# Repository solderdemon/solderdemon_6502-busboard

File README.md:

# SolderDemon 6502 Bus Board

## Overview

A 5-slot expansion busboard for the SolderDemon 6502 computer. The 36-pin bus keeps the [rosco_6502](https://github.com/rosco-m68k/rosco_6502) pin order, so cards made for that bus fit.

Designed as a modular vertical-card backplane architecture featuring 1 dedicated host connection for the SolderDemon 6502 CPU board and 4 peripheral expansion slots (e.g., RAM boards, I/O controllers), along with flexible 5V power delivery and host isolation options.

## Start here

- [KiCad project](design/solderdemon_6502-busboard.kicad_pro)
- [Schematic (PDF)](manufacturing/solderdemon_6502-busboard-schematic.pdf)
- [Host mounting and first build](#host-mounting-and-first-build)
- [Gerbers and drill files](manufacturing/solderdemon_6502-busboard-gerbers.zip)
- [Assembly BOM](manufacturing/bom.csv)

## Board views

*Prototype photo with edited background and lighting.*

| Top Side | Bottom Side |
|:---:|:---:|
|  |  |

## Hardware

### Highlights

- **Slot Architecture:** 1 Host Slot (`BUS1`) + 4 Expansion Slots (`BUS2`–`BUS5` = SLOT 1–4, each with its 100 nF `C3`–`C6`) using standard 2×18 vertical pin headers (2.54 mm / 0.1" pitch, 20 mm slot pitch). The host and the cards stand upright in their slots on right-angle 2×18 sockets, all facing the same way; a silkscreen triangle marks pin 1 of every slot; as on the SolderDemon m68k busboard, each slot's decoupler stands on the half-pitch line to its right, beside pin 1, clear of every board plane
- **Power Inputs:** Triple 5V power input options:
  - USB Type-C receptacle (`J3`, USB 2.0 power delivery with onboard 5.1 kΩ CC pull-downs)
  - 5.5 / 2.1 mm DC Barrel Jack (`J1`, center-positive)
  - 2-pin screw terminal / vertical header block (`J2`, 5V IN)
- **Source Selection:** one jumper cap on the 2×3 header `JP2` picks the input: the USB, DC or TERM row, in the order of the inputs down the right edge (USB-C, DC jack, then the terminal `J2` under the jack). No diodes, so no 0.3–0.6 V drop: the bus gets the supply voltage. Never fit two source jumpers
- **Protection:** a 1.5KE6.8A unidirectional TVS (`D1`) from `VCC` to GND. There is no fuse: a reversed or wrong-voltage adapter is shorted by `D1`, and only the adapter's own current limit stops it
- **Power Control & Filtering:** NKK M2021SS1W01 DPST toggle (`SW1`, the switch of the SolderDemon m68k busboard; both poles in parallel), PWR GOOD LED indicator (`LED1`), 470 µF bulk electrolytic reservoir (`C1`), five 100 nF bypass capacitors (`C2`–`C6`) and the bus `~RESET` pull-up `R2` with `C7`
- **Host Power Isolation (`JP1`):** Allows powering the host SBC independently (e.g., via USB serial adapter) while powering peripheral slots from the backplane
- **Form Factor:** 137 × 100 mm 2-layer PCB, all through-hole components (except USB-C receptacle) for straightforward DIY assembly
- **Mounting:** 6× M3 mounting holes with grounded annular pads, three along each long edge: the four corners plus the middle of the top and bottom edge, halfway between the corner holes

### Pinout

The busboard exposes the 36-pin SolderDemon 6502 bus (rosco_6502-compatible pin order) across all five slots:

| Pin | Signal | Description | Pin | Signal | Description |
|:---:|:---|:---|:---:|:---|:---|
| **1** | **A0** | Address Bus bit 0 (square pad) | **2** | **VCC / VCC_HOST** | +5V Power Rail (Host isolated via JP1) |
| **3** | **A1** | Address Bus bit 1 | **4** | **CLK** | CPU Phase 2 System Clock (PHI2) |
| **5** | **A2** | Address Bus bit 2 | **6** | **GND** | System Ground (0V) |
| **7** | **A3** | Address Bus bit 3 | **8** | **R/~W** | Read / ~Write Control Line |
| **9** | **A4** | Address Bus bit 4 | **10** | **~RESET** | Active-Low System Reset |
| **11** | **A5** | Address Bus bit 5 | **12** | **RDY** | 65C02 CPU Ready Line |
| **13** | **A6** | Address Bus bit 6 | **14** | **~NMI** | Non-Maskable Interrupt Request |
| **15** | **A7** | Address Bus bit 7 | **16** | **~IRQ** | Maskable Interrupt Request |
| **17** | **A8** | Address Bus bit 8 | **18** | **SYNC** | Opcode Fetch Cycle Indicator |
| **19** | **A9** | Address Bus bit 9 | **20** | **BE** | Bus Enable Line |
| **21** | **A10** | Address Bus bit 10 | **22** | **D7** | Data Bus bit 7 |
| **23** | **A11** | Address Bus bit 11 | **24** | **D6** | Data Bus bit 6 |
| **25** | **A12** | Address Bus bit 12 | **26** | **D5** | Data Bus bit 5 |
| **27** | **A13** | Address Bus bit 13 | **28** | **D4** | Data Bus bit 4 |
| **29** | **A14** | Address Bus bit 14 | **30** | **D3** | Data Bus bit 3 |
| **31** | **A15** | Address Bus bit 15 | **32** | **D2** | Data Bus bit 2 |
| **33** | **~VP** | Vector Pull Indicator | **34** | **D1** | Data Bus bit 1 |
| **35** | **~ML** | Memory Lock Indicator | **36** | **D0** | Data Bus bit 0 |

#### Power Interfaces & Control

| Designator | Label | Type / Footprint | Description |
|:---|:---|:---|:---|
| **J1** | DC IN | Barrel Jack 5.5 / 2.1 mm | 5V DC power input (center-positive) |
| **J2** | 5V IN | Pin Header / Terminal 1×02 | Auxiliary 5V DC power input, on the right edge under the DC jack |
| **J3** | USB-C 5V | USB Type-C Receptacle | 5V DC USB power input with CC pull-down resistors |
| **JP2** | SOURCE | Pin Header 2×03, 2.54 mm | Source select: one jumper cap across the USB, DC or TERM row |
| **SW1** | POWER | NKK M2021SS1W01 DPST toggle | Main power ON / OFF switch |
| **JP1** | PWR LINK | Pin Header 1×02, 2.54 mm | Power link jumper: links `VCC_HOST` to bus `VCC` |

> **Note on JP1 (PWR LINK):** When jumpered (default), all slots share the busboard 5V rail. When unjumpered, the host slot (`BUS1`) receives power from its own onboard source or serial adapter, preventing current loops while still sharing ground and signals.

## Using the board

### Host mounting and first build

The SolderDemon 6502 r1 host carries a right-angle female 2×18 socket on its J5 pads (KiCad `PinSocket_2x18_P2.54mm_Horizontal`; pin 2 is the pad nearer the body, i.e. the pads are the stock header mirrored) and stands upright in HOST, component side toward the busboard's left edge, its top edge level with the busboard's top edge. The compact SolderDemon 6502 RAM card uses the mirrored socket on B.Cu at its **right** edge and stands with its component side toward the next slot. Its pin 1 must align with the triangle at the top of the slot; all 36 contacts and the mirrored footprint geometry are checked against the current PCB files by its `tools/check_design.py`. Bolt the busboard through its six M3 holes to a case or rigid base before inserting any board. Do not connect J5 to HOST with a ribbon cable instead: because J5's pin order is mirrored for the socket, a plain 36-way ribbon between J5 and the straight HOST header swaps every odd/even pair and puts `VCC` on `A0`. The mating model (contact-row heights, edge height, clearances) is in [BACKPLANE.md](BACKPLANE.md).

The selected input carries the full board load through `SW1`; measure total current and voltage at the farthest slot before populating all five slots. The first order should be a prototype run, followed by pin-1 continuity, power and loaded-voltage checks.

## Build and verification

### Bill of Materials (BOM)

| Reference | Value | Package / Footprint | Notes |
|:---|:---|:---|:---|
| **BUS1–BUS5** | Conn_02x18 | PinHeader 2×18, 2.54 mm, Vertical | Host slot (`BUS1`) & 4 expansion slots (`BUS2`–`BUS5`) |
| **J1** | Barrel Jack | BarrelJack_Horizontal 5.5 / 2.1 mm | 5V DC input |
| **J2** | Conn_01x02 | PinHeader 1×02, 2.54 mm, Vertical | Auxiliary 5V screw terminal or pin header |
| **J3** | USB-C 16P | USB4105-xx-A Top Mount | USB Type-C 5V power receptacle |
| **JP1** | Conn_01x02 | PinHeader 1×02, 2.54 mm, Vertical | PWR LINK host power isolation jumper |
| **JP2** | Conn_02x03 + one jumper cap | PinHeader 2×03, 2.54 mm, Vertical | Source select: odd pins 1 terminal, 3 DC jack, 5 USB-C; even pins the common input |
| **D1** | 1.5KE6.8A | DO-201AE, Axial (THT) | Unidirectional TVS, 5.8 V standoff, across `VCC` |
| **SW1** | NKK M2021SS1W01 | NKK-M2021SS1W01 (SolderDemon.pretty) | DPST ON-OFF toggle, both poles in parallel; as on the m68k busboard |
| **LED1** | LED 5 mm | Radial D5.0 mm (THT) | PWR GOOD 5V rail status indicator |
| **C1** | 470 µF | Radial D6.3 mm, P2.5 mm | Bulk electrolytic reservoir capacitor |
| **C2–C6** | 100 nF | Radial 5.08 mm pitch | Decoupling: `C2` HOST, `C3`–`C6` SLOT 1–4 |
| **C7** | 1 nF | Disc D5.0 mm, P2.5 mm | Bus `~RESET` noise capacitor, with `R2`. Small on purpose: the host drives `~RESET` open-drain from its CPLD with its own 3.3 kΩ pull-up, and 100 nF would dump into that pin on every reset and stretch the release to ~250 µs |
| **R1** | 1 kΩ | Axial DIN0207, P10.16 mm | Current-limiting resistor for LED1 |
| **R2** | 10 kΩ | Axial DIN0207, P10.16 mm | Bus `~RESET` pull-up |
| **R3, R4** | 5.1 kΩ | Axial DIN0207, P10.16 mm | USB Type-C CC1 / CC2 pull-down resistors |
| **H1–H6** | Mounting Hole | 3.2 mm M3 with Ground Pad | Corners (`H1`–`H4`), middle of the top and bottom edge (`H5`, `H6`) |

### Manufacturing & Hardware Files

- **KiCad Project:** [design/](design/)
- **Footprint Libraries:** `SolderDemon.pretty/` (logo), `SolderDemonBus.pretty/`, `SolderDemonDirectMount.pretty/`
- **Schematic PDF:** [SolderDemon 6502 busboard schematic](manufacturing/solderdemon_6502-busboard-schematic.pdf)
- **Gerbers:**
  - Prototype fabrication archive: [solderdemon_6502-busboard-gerbers.zip](manufacturing/solderdemon_6502-busboard-gerbers.zip)
  - Unpacked fresh layers in [manufacturing/gerber/](manufacturing/gerber/) folder
- **PCB Specs:** 2-layer board, 137 × 100 mm, 1.6 mm thickness, standard 1 oz copper, HASL / ENIG finish
- **Design Verification:** [DRC Report](solderdemon_6502-busboard-drc.rpt) (KiCad 10.0.8 reports 4 hole-clearance errors at J3, 0 unrouted pads and 35 schematic-parity warnings), [ERC Report](solderdemon_6502-busboard-erc.rpt) (0 violations)
- **Backplane Specification:** [BACKPLANE.md](BACKPLANE.md) — mechanical dimensions, slot spacing, connector mating, and daughterboard form factor guidelines.

### Fabrication status

The current files are for prototype review. KiCad 10.0.8 reports four hole-clearance errors at USB-C connector J3. Review those clearances before fabrication.

<!-- repository-layout -->
## Repository layout

- [`design/`](design/solderdemon_6502-busboard.kicad_pro) holds the KiCad project, schematic, PCB and local libraries.
- [`code/firmware/`](code/firmware/) — This busboard has no programmable devices.
- [`code/software/`](code/software/) — The backplane requires no drivers or applications.
- [`code/build/`](code/build/) — Local build products.
- [`tools/`](tools/) — Design generators and verification.
- [`manufacturing/`](manufacturing/) — Fabrication files and schematic PDF.
- [`images/`](images/) — Board views and artwork.

Open the project in `design/`. Use the scripts in `tools/` to change the design. The `.kicad_pro` file holds the DRC rules.
<!-- /repository-layout -->

## Licences and attribution

- **Hardware:** [CERN Open Hardware Licence v1.2](LICENCE.hardware.txt).
- **Documentation:** [Creative Commons Attribution 4.0](https://creativecommons.org/licenses/by/4.0/).

SolderDemon backplane for the [rosco_6502](https://github.com/rosco-m68k/rosco_6502) expansion interface. Original rosco_6502 authorship: Ross Bamford & Contributors. Retained source and third-party notices identify their respective authors.

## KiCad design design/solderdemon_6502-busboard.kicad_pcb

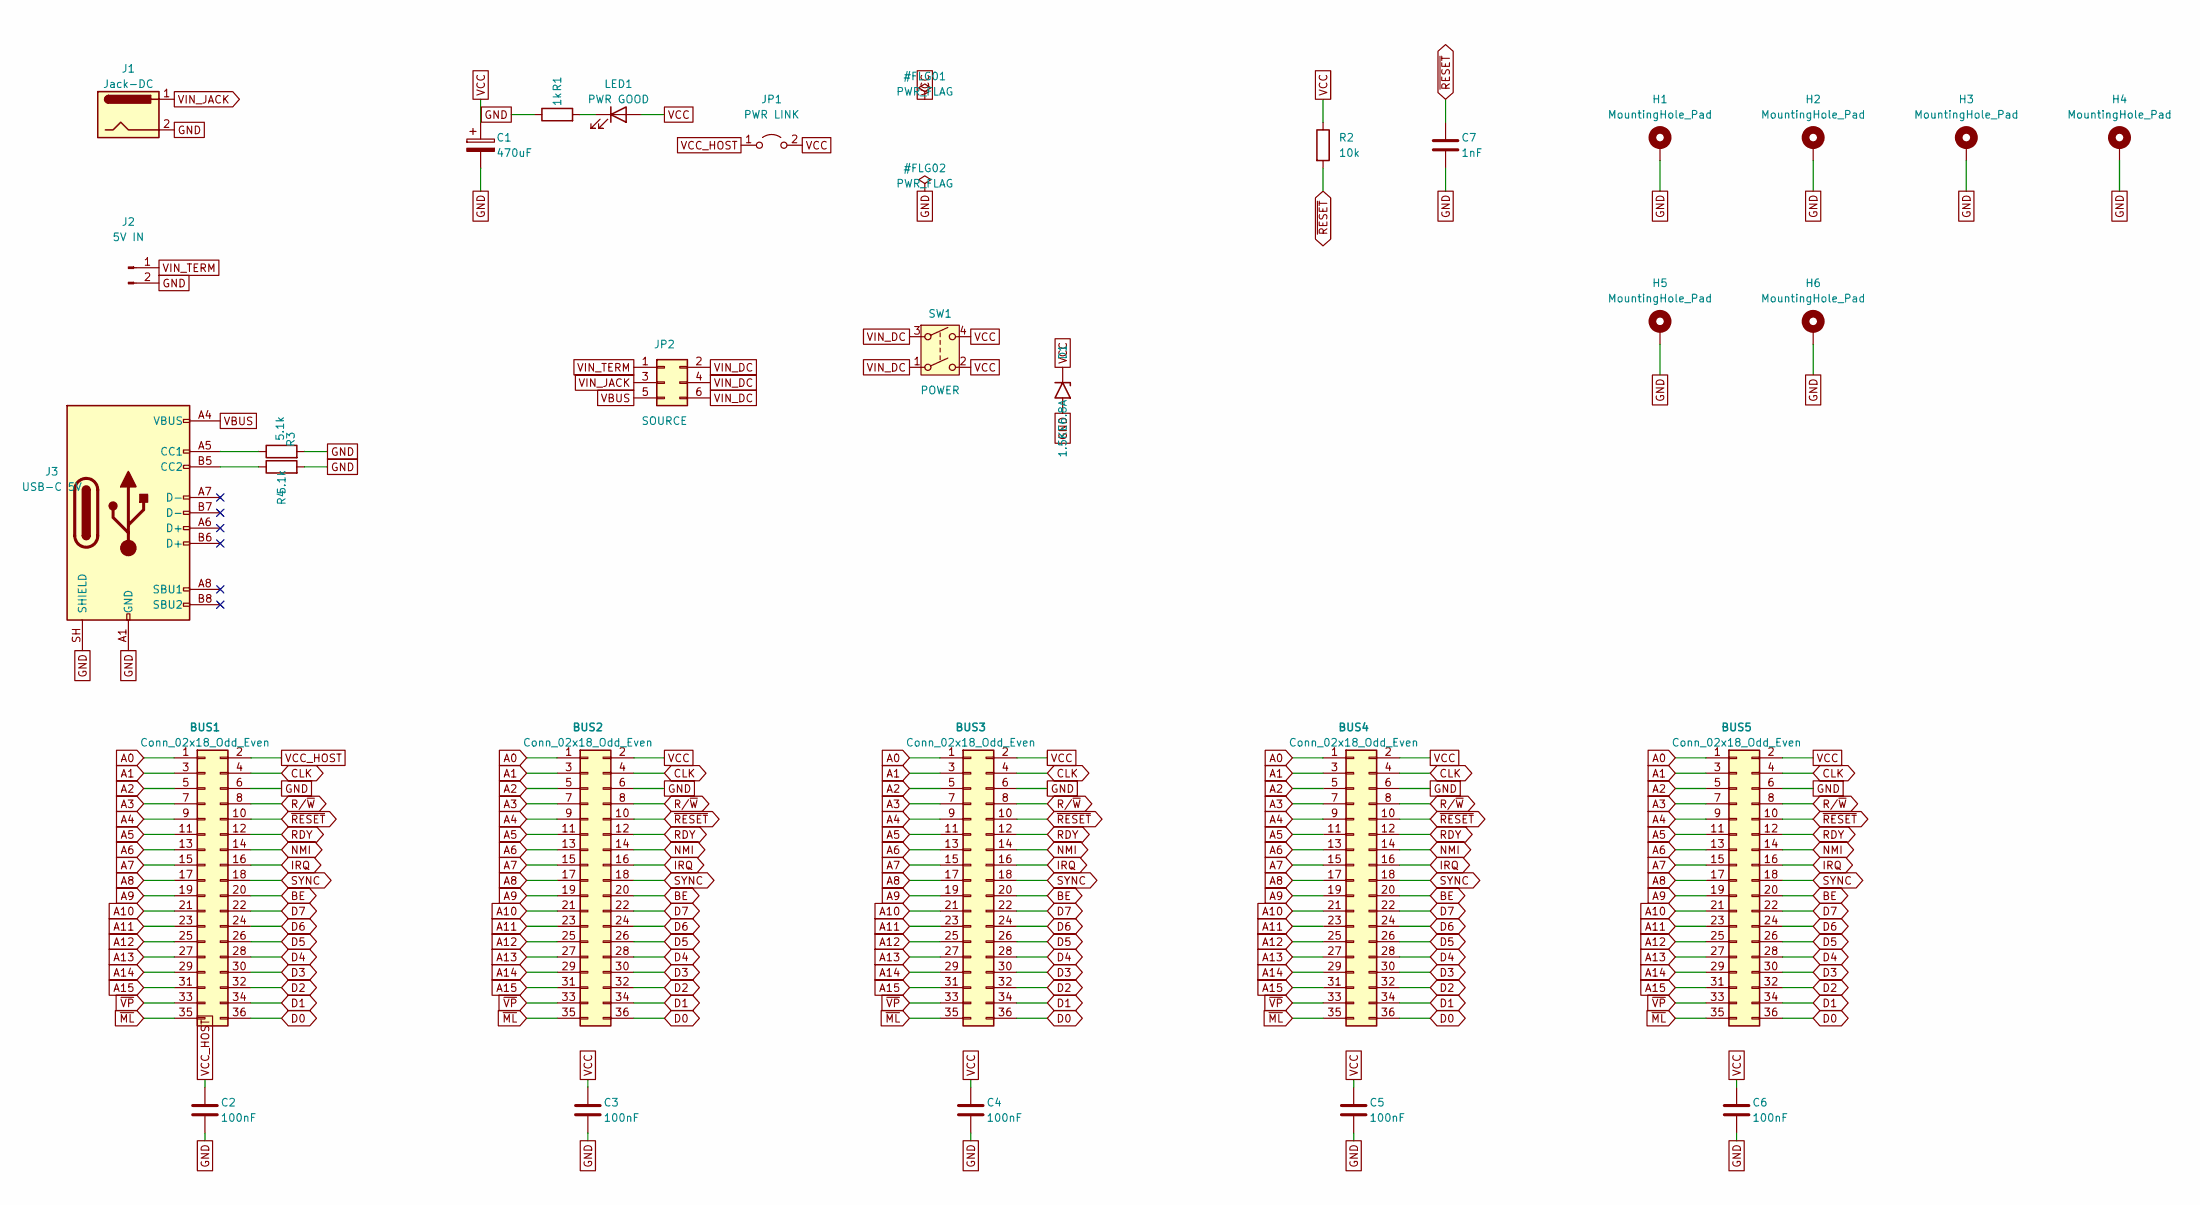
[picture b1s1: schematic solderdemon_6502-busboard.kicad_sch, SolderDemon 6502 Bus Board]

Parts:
BUS1, BUS2, BUS3, BUS4, BUS5: Conn_02x18_Odd_Even; PinHeader_2x18_P2.54mm_Vertical
C1: 470uF; CP_Radial_D6.3mm_P2.50mm
C2, C3, C4, C5, C6: 100nF; C_Radial_5.08mm
C7: 1nF; C_Disc_D5.0mm_W2.5mm_P2.50mm
D1: 1.5KE6.8A; D_DO-201AE_P15.24mm_Horizontal
H1, H2, H3, H4, H5, H6: MountingHole_Pad; MountingHole_3.2mm_M3_Pad
J1: Jack-DC; BarrelJack_Horizontal
J2: 5V IN; PinHeader_1x02_P2.54mm_Vertical
J3: USB-C 5V; USB_C_Receptacle_GCT_USB4105-xx-A_16P_TopMnt_Horizontal
JP1: PWR LINK; PinHeader_1x02_P2.54mm_Vertical
JP2: SOURCE; PinHeader_2x03_P2.54mm_Vertical
LED1: PWR GOOD; LED_D5.0mm
R1: 1k; R_Axial_DIN0207_L6.3mm_D2.5mm_P10.16mm_Horizontal
R2: 10k; R_Axial_DIN0207_L6.3mm_D2.5mm_P10.16mm_Horizontal
R3, R4: 5.1k; R_Axial_DIN0207_L6.3mm_D2.5mm_P10.16mm_Horizontal
SW1: POWER; NKK-M2021SS1W01

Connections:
A0: BUS1.1, BUS2.1, BUS3.1, BUS4.1, BUS5.1
A1: BUS1.3, BUS2.3, BUS3.3, BUS4.3, BUS5.3
A2: BUS1.5, BUS2.5, BUS3.5, BUS4.5, BUS5.5
A3: BUS1.7, BUS2.7, BUS3.7, BUS4.7, BUS5.7
A4: BUS1.9, BUS2.9, BUS3.9, BUS4.9, BUS5.9
A5: BUS1.11, BUS2.11, BUS3.11, BUS4.11, BUS5.11
A6: BUS1.13, BUS2.13, BUS3.13, BUS4.13, BUS5.13
A7: BUS1.15, BUS2.15, BUS3.15, BUS4.15, BUS5.15
A8: BUS1.17, BUS2.17, BUS3.17, BUS4.17, BUS5.17
A9: BUS1.19, BUS2.19, BUS3.19, BUS4.19, BUS5.19
A10: BUS1.21, BUS2.21, BUS3.21, BUS4.21, BUS5.21
A11: BUS1.23, BUS2.23, BUS3.23, BUS4.23, BUS5.23
A12: BUS1.25, BUS2.25, BUS3.25, BUS4.25, BUS5.25
A13: BUS1.27, BUS2.27, BUS3.27, BUS4.27, BUS5.27
A14: BUS1.29, BUS2.29, BUS3.29, BUS4.29, BUS5.29
A15: BUS1.31, BUS2.31, BUS3.31, BUS4.31, BUS5.31
BE: BUS1.20, BUS2.20, BUS3.20, BUS4.20, BUS5.20
CLK: BUS1.4, BUS2.4, BUS3.4, BUS4.4, BUS5.4
D0: BUS1.36, BUS2.36, BUS3.36, BUS4.36, BUS5.36
D1: BUS1.34, BUS2.34, BUS3.34, BUS4.34, BUS5.34
D2: BUS1.32, BUS2.32, BUS3.32, BUS4.32, BUS5.32
D3: BUS1.30, BUS2.30, BUS3.30, BUS4.30, BUS5.30
D4: BUS1.28, BUS2.28, BUS3.28, BUS4.28, BUS5.28
D5: BUS1.26, BUS2.26, BUS3.26, BUS4.26, BUS5.26
D6: BUS1.24, BUS2.24, BUS3.24, BUS4.24, BUS5.24
D7: BUS1.22, BUS2.22, BUS3.22, BUS4.22, BUS5.22
GND: BUS1.6, BUS2.6, BUS3.6, BUS4.6, BUS5.6, C1.2, C2.2, C3.2, C4.2, C5.2, C6.2, C7.2, D1.2 (A2), H1.1, H2.1, H3.1, H4.1, H5.1, H6.1, J1.2, J2.2, J3.A1 (GND), J3.A12 (GND), J3.B1 (GND), J3.B12 (GND), J3.SH (SHIELD), R1.1, R3.2, R4.2
IRQ: BUS1.16, BUS2.16, BUS3.16, BUS4.16, BUS5.16
NMI: BUS1.14, BUS2.14, BUS3.14, BUS4.14, BUS5.14
unnamed: J3.A5 (CC1), R3.1
unnamed: J3.B5 (CC2), R4.1
unnamed: LED1.1 (K), R1.2
RDY: BUS1.12, BUS2.12, BUS3.12, BUS4.12, BUS5.12
R/~W: BUS1.8, BUS2.8, BUS3.8, BUS4.8, BUS5.8
SYNC: BUS1.18, BUS2.18, BUS3.18, BUS4.18, BUS5.18
VBUS: J3.A4 (VBUS), J3.A9 (VBUS), J3.B4 (VBUS), J3.B9 (VBUS), JP2.5
VCC: BUS2.2, BUS3.2, BUS4.2, BUS5.2, C1.1, C3.1, C4.1, C5.1, C6.1, D1.1 (A1), JP1.2 (B), LED1.2 (A), R2.1, SW1.2, SW1.4
VCC_HOST: BUS1.2, C2.1, JP1.1 (A)
VIN_DC: JP2.2, JP2.4, JP2.6, SW1.1, SW1.3
VIN_JACK: J1.1, JP2.3
VIN_TERM: J2.1, JP2.1
~ML: BUS1.35, BUS2.35, BUS3.35, BUS4.35, BUS5.35
~RESET: BUS1.10, BUS2.10, BUS3.10, BUS4.10, BUS5.10, C7.1, R2.2
~VP: BUS1.33, BUS2.33, BUS3.33, BUS4.33, BUS5.33

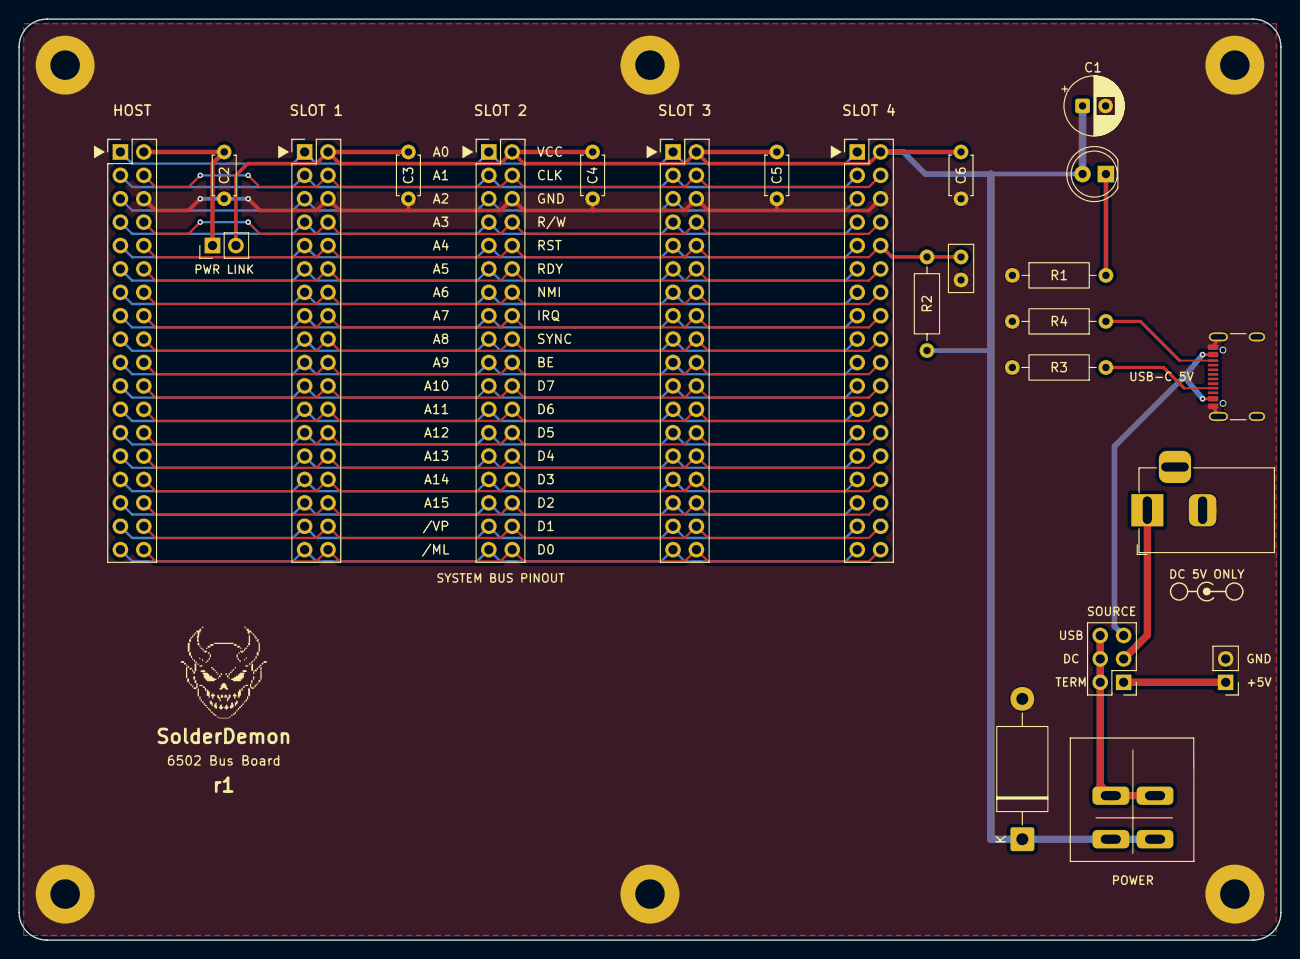
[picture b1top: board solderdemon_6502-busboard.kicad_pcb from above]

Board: 2 copper layers, 137.0 x 100.0 mm, 31 parts (0 on the bottom side), 44 nets.

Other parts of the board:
LOGO1: SolderDemon_Logo

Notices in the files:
design/solderdemon_6502-busboard.kicad_pcb:
© 2026 SolderDemon
design/solderdemon_6502-busboard.kicad_sch:
CERN Open Hardware Licence Version 2 - Strongly Reciprocal
